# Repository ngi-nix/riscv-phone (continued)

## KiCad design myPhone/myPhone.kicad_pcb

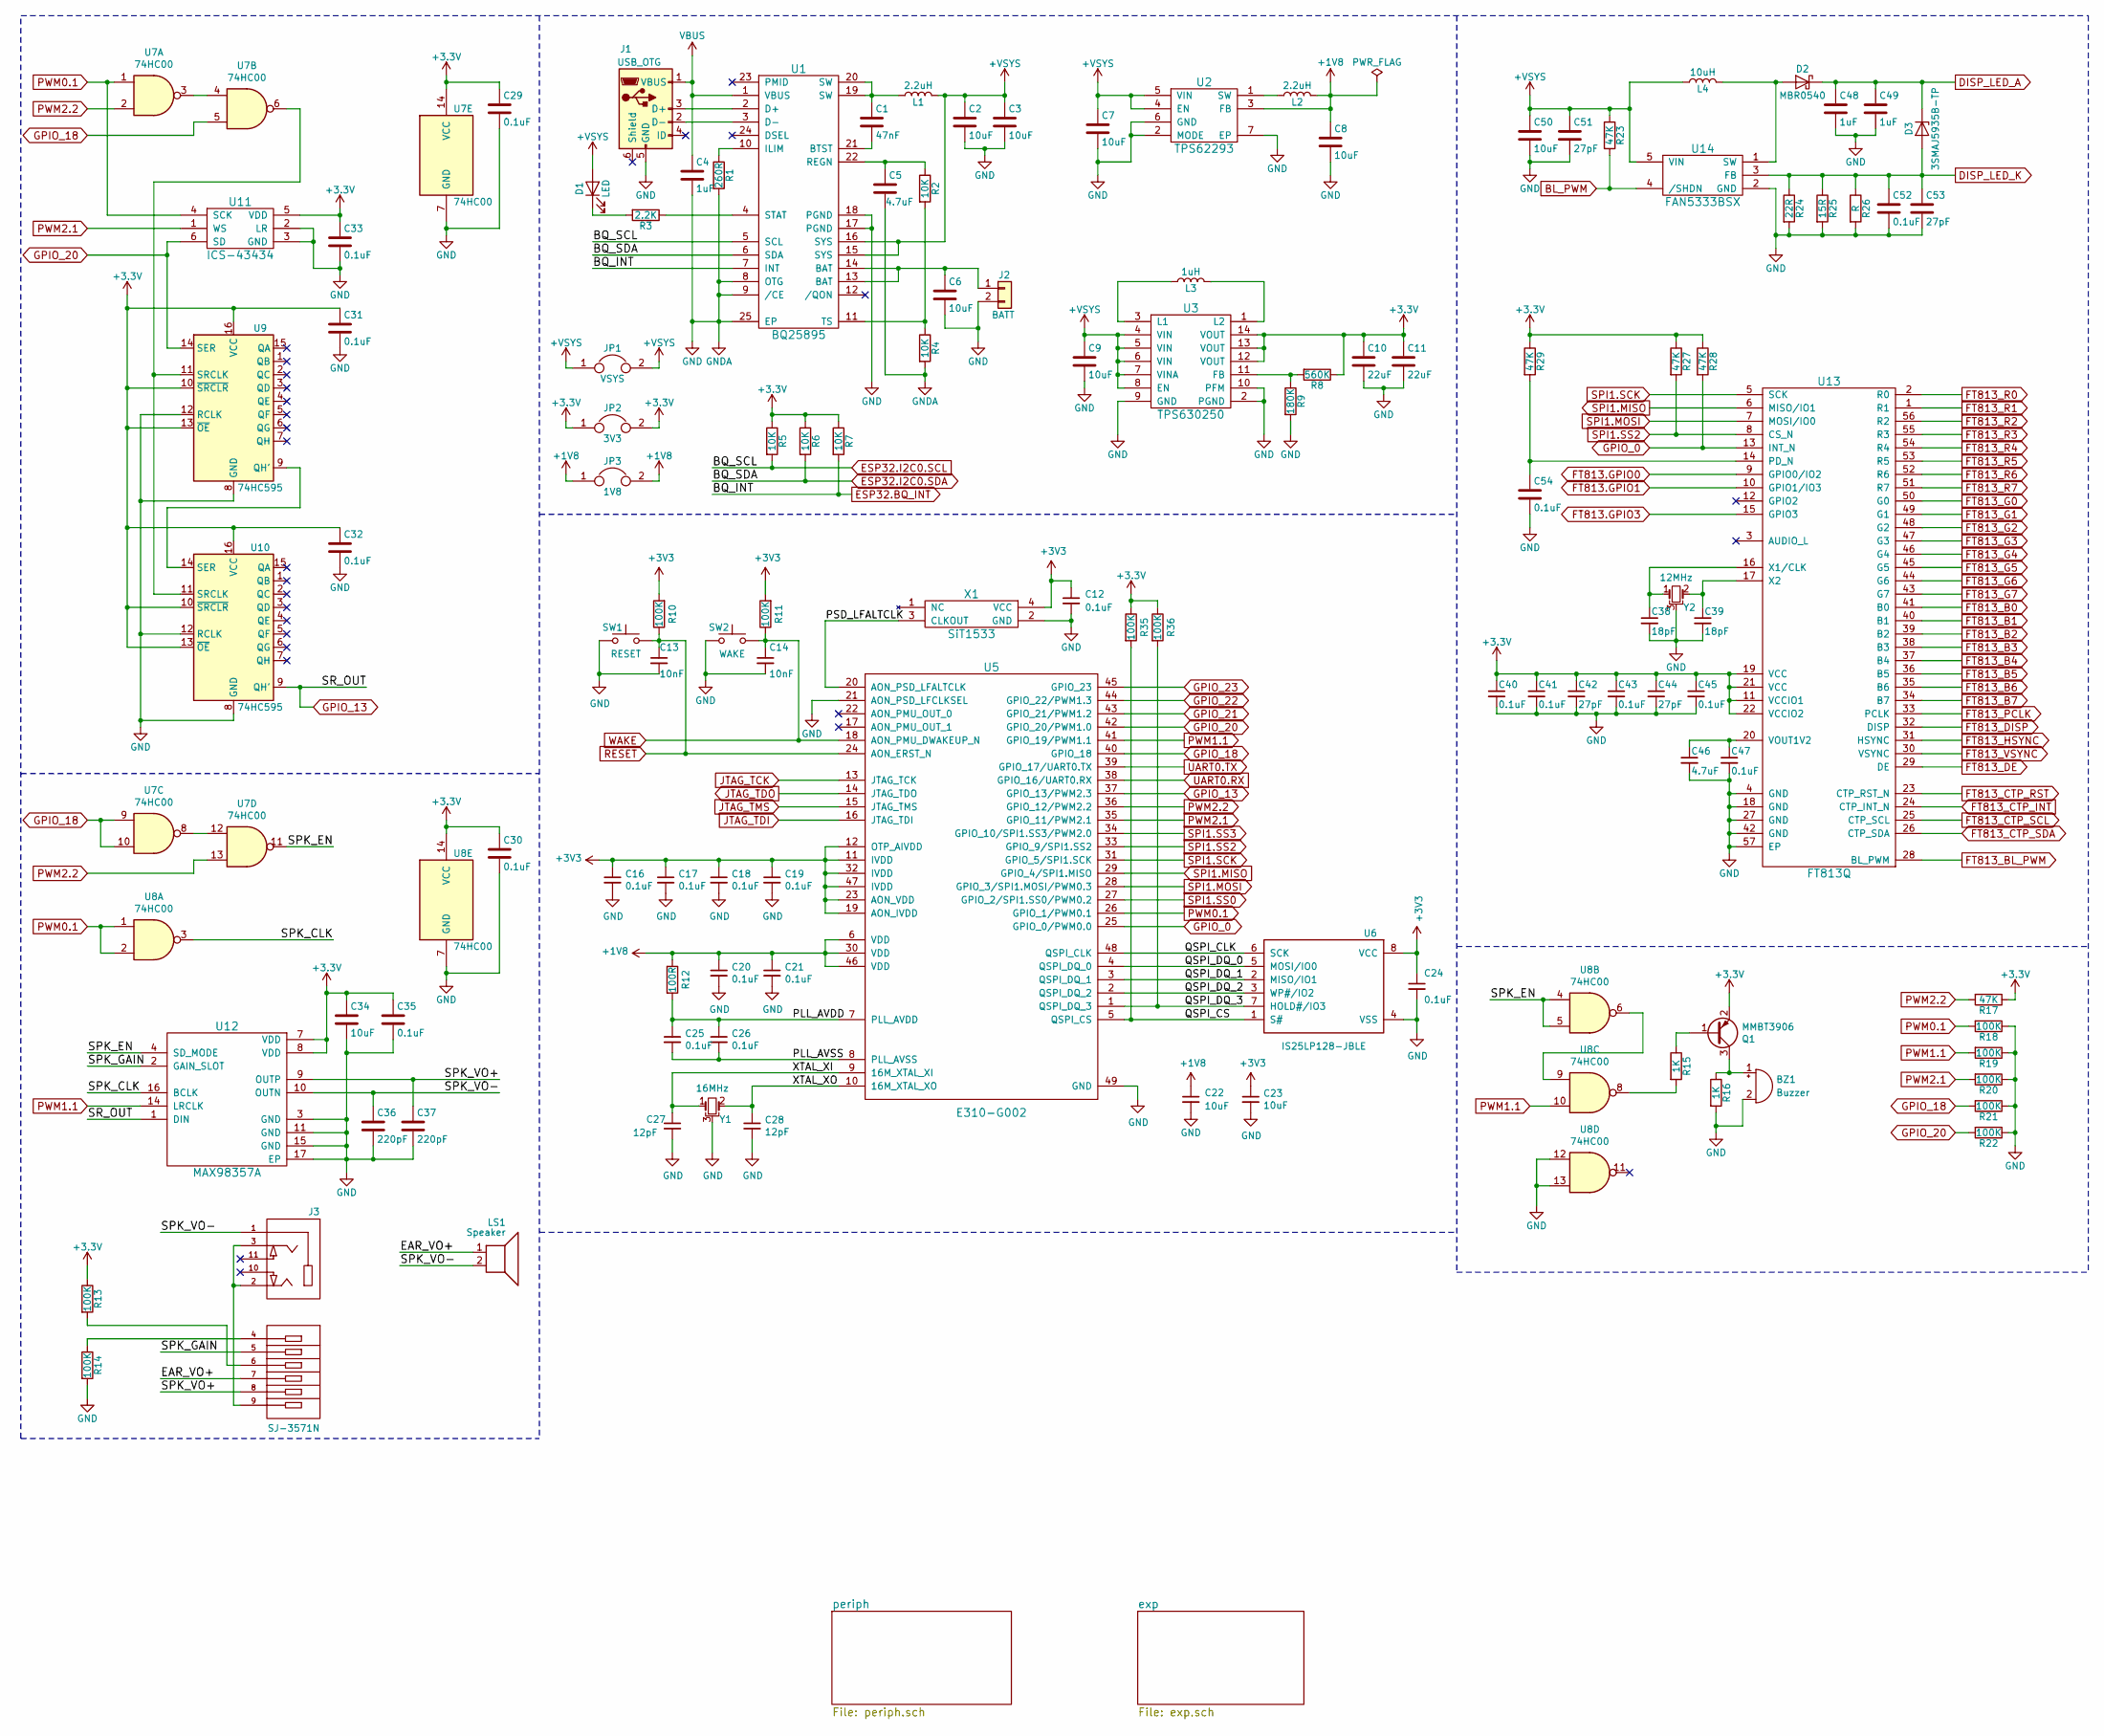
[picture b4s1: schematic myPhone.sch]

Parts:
BZ1: Buzzer; Buzzer_12x9.5RM5.0
C1: 47nF; C_0603_1608Metric
C2, C3, C6, C7, C8, C9, C22, C23, C34, C50: 10uF; C_0603_1608Metric
C4, C48, C49: 1uF; C_0603_1608Metric
C5, C46: 4.7uF; C_0603_1608Metric
C10, C11: 22uF; C_0603_1608Metric
C12, C16, C17, C18, C19, C20, C21, C24, C25, C26, C29, C30, C31, C32, C33, C35, C40, C41, C43, C45, C47, C52, C54: 0.1uF; C_0603_1608Metric
C13, C14: 10nF; C_0603_1608Metric
C27, C28: 12pF; C_0603_1608Metric
C36, C37: 220pF; C_0603_1608Metric
C38, C39: 18pF; C_0603_1608Metric
C42, C44, C51, C53: 27pF; C_0603_1608Metric
D1: LED; LED_0603_1608Metric
D2: MBR0540; D_SOD-123
D3: 3SMAJ5935B-TP; D_SMA
J1: USB_OTG; USB_Micro-B
J2: BATT; PinHeader_1x02_P2.00mm_Vertical
J3: SJ-3571N; CUI_SJ-3571N
JP1: VSYS; PinHeader_1x02_P1.27mm_Vertical
JP2: 3V3; PinHeader_1x02_P1.27mm_Vertical
JP3: 1V8; PinHeader_1x02_P1.27mm_Vertical
L1, L2: 2.2uH; L_Coilcraft_LPS3015
L3: 1uH; L_Coilcraft_XAL40
L4: 10uH; L_Murata_LQH66SN
LS1: Speaker; PinHeader_1x02_P1.27mm_Vertical
Q1: MMBT3906; SOT-23
R1: 260R; R_0603_1608Metric
R2, R4, R5, R6, R7: 10K; R_0603_1608Metric
R3: 2.2K; R_0603_1608Metric
R8: 560K; R_0603_1608Metric
R9: 180K; R_0603_1608Metric
R10, R11, R13, R14, R18, R19, R20, R21, R22, R35, R36: 100K; R_0603_1608Metric
R12: 100R; R_0603_1608Metric
R15, R16: 1K; R_0603_1608Metric
R17, R23, R27, R28, R29: 47K; R_0603_1608Metric
R24: 22R; R_0603_1608Metric
R25: 15R; R_0603_1608Metric
R26: R; R_0603_1608Metric
SW1: RESET; Panasonic_EVPBB
SW2: WAKE; Panasonic_EVPAK
U1: BQ25895; Texas_S-PWQFN-N24_EP2.7x2.7mm_ThermalVias
U2: TPS62293; TPS62290
U3: TPS630250
U5: E310-G002; QFN-48-1EP_6x6mm_P0.4mm_EP4.2x4.2mm_ThermalVias
U6: IS25LP128-JBLE; SOIJ-8_5.3x5.3mm_P1.27mm
U7, U8: 74HC00; 74HC00BQ115
U9, U10: 74HC595; 74HC595BQ115
U11: ICS-43434; TDK_ICS-43434
U12: MAX98357A; TQFN-16-1EP_3x3mm_P0.5mm_EP1.23x1.23mm_ThermalVias
U13: FT813Q; QFN-56-1EP_8x8mm_P0.5mm_EP5.6x5.6mm_ThermalVias
U14: FAN5333BSX; SOT-23-5
X1: SiT1533
Y1: 16MHz; TXC_7M
Y2: 12MHz; TXC_7M

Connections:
+1V8: C8.1, C20.1, C21.1, C22.1, JP3.1, JP3.2, L2.2, R12.1, U2.3 (FB), U5.6 (VDD), U5.30 (VDD), U5.46 (VDD); also elsewhere on the board
+VSYS: C2.1, C3.1, C7.1, C9.1, C50.1, C51.1, D1.2 (A), JP1.1, JP1.2, L1.2, L4.1, R23.1, U1.15 (SYS), U1.16 (SYS), U2.4 (EN), U2.5 (VIN), U3.4 (VIN), U3.5 (VIN), U3.6 (VIN), U3.7 (VINA), U3.8 (EN), U14.5 (VIN); also elsewhere on the board
/EAR_VO+: J3.7, LS1.1
/PLL_AVDD: C25.1, C26.1, R12.2, U5.7 (PLL_AVDD)
/PLL_AVSS: C25.2, C26.2, U5.8 (PLL_AVSS)
/PSD_LFALTCLK: U5.20 (AON_PSD_LFALTCLK), X1.3 (CLKOUT)
/QSPI_CLK: U5.48 (QSPI_CLK), U6.6 (SCK)
/QSPI_CS: R35.2, U5.5 (QSPI_CS), U6.1 (S#)
/QSPI_DQ_0: U5.4 (QSPI_DQ_0), U6.5 (MOSI/IO0)
/QSPI_DQ_1: U5.3 (QSPI_DQ_1), U6.2 (MISO/IO1)
/QSPI_DQ_2: U5.2 (QSPI_DQ_2), U6.3 (WP#/IO2)
/QSPI_DQ_3: R36.2, U5.1 (QSPI_DQ_3), U6.7 (HOLD#/IO3)
/SPK_CLK: U8.3, U12.16 (BCLK)
/SPK_EN: U7.11, U8.4, U8.5, U12.4 (SD_MODE); also elsewhere on the board
/SPK_GAIN: J3.5, U12.2 (GAIN_SLOT)
/SPK_VO+: C37.1, J3.8, U12.9 (OUTP)
/SPK_VO-: C36.1, J3.1, LS1.2, U12.10 (OUTN)
/XTAL_XI: C27.1, U5.9 (16M_XTAL_XI), Y1.1
/XTAL_XO: C28.1, U5.10 (16M_XTAL_XO), Y1.2
BL_PWM: R23.2, U14.4 (/SHDN); also elsewhere on the board
DISP_LED_A: C48.1, C49.1, D2.1 (K), D3.1 (K); also elsewhere on the board
DISP_LED_K: C52.1, C53.1, D3.2 (A), R24.1, R25.1, R26.1, U14.3 (FB); also elsewhere on the board
ESP32.IO39: R7.2, U1.7 (INT); also elsewhere on the board
FT813.GPIO0: U13.9 (GPIO0/IO2); also elsewhere on the board
FT813.GPIO1: U13.10 (GPIO1/IO3); also elsewhere on the board
FT813.GPIO3: U13.15 (GPIO3); also elsewhere on the board
FT813_B0: U13.41 (B0); also elsewhere on the board
FT813_B1: U13.40 (B1); also elsewhere on the board
FT813_B2: U13.39 (B2); also elsewhere on the board
FT813_B3: U13.38 (B3); also elsewhere on the board
FT813_B4: U13.37 (B4); also elsewhere on the board
FT813_B5: U13.36 (B5); also elsewhere on the board
FT813_B6: U13.35 (B6); also elsewhere on the board
FT813_B7: U13.34 (B7); also elsewhere on the board
FT813_BL_PWM: U13.28 (BL_PWM); also elsewhere on the board
FT813_CTP_INT: U13.24 (CTP_INT_N); also elsewhere on the board
FT813_CTP_RST: U13.23 (CTP_RST_N); also elsewhere on the board
FT813_CTP_SCL: U13.25 (CTP_SCL); also elsewhere on the board
FT813_CTP_SDA: U13.26 (CTP_SDA); also elsewhere on the board
FT813_DE: U13.29 (DE); also elsewhere on the board
FT813_DISP: U13.32 (DISP); also elsewhere on the board
FT813_G0: U13.50 (G0); also elsewhere on the board
FT813_G1: U13.49 (G1); also elsewhere on the board
FT813_G2: U13.48 (G2); also elsewhere on the board
FT813_G3: U13.47 (G3); also elsewhere on the board
FT813_G4: U13.46 (G4); also elsewhere on the board
FT813_G5: U13.45 (G5); also elsewhere on the board
FT813_G6: U13.44 (G6); also elsewhere on the board
FT813_G7: U13.43 (G7); also elsewhere on the board
FT813_HSYNC: U13.31 (HSYNC); also elsewhere on the board
FT813_PCLK: U13.33 (PCLK); also elsewhere on the board
FT813_R0: U13.2 (R0); also elsewhere on the board
FT813_R1: U13.1 (R1); also elsewhere on the board
FT813_R2: U13.56 (R2); also elsewhere on the board
FT813_R3: U13.55 (R3); also elsewhere on the board
FT813_R4: U13.54 (R4); also elsewhere on the board
FT813_R5: U13.53 (R5); also elsewhere on the board
FT813_R6: U13.52 (R6); also elsewhere on the board
FT813_R7: U13.51 (R7); also elsewhere on the board
FT813_VSYNC: U13.30 (VSYNC); also elsewhere on the board
GND: BZ1.2 (+), C2.2, C3.2, C4.2, C5.2, C6.2, C7.2, C8.2, C9.2, C10.2, C11.2, C12.2, C13.2, C14.2, C16.2, C17.2, C18.2, C19.2, C20.2, C21.2, C22.2, C23.2, C24.2, C27.2, C28.2, C29.2, C30.2, C31.2, C32.2, C33.2, C34.2, C35.2, C36.2, C37.2, C38.2, C39.2, C40.2, C41.2, C42.2, C43.2, C44.2, C45.2, C46.2, C47.2, C48.2, C49.2, C50.2, C51.2, C52.2, C53.2, C54.2, J1.5 (GND), J2.2, R1.2, R4.2, R9.2, R14.2, R16.2, R18.1, R19.1, R20.1, R21.1, R22.1, R24.2, R25.2, R26.2, SW1.1, SW2.2, U1.8 (OTG), U1.9 (/CE), U1.17 (PGND), U1.18 (PGND), U1.25 (EP), U2.2 (MODE), U2.6 (GND), U2.7 (EP), U3.2 (PGND), U3.9 (GND), U3.10 (PFM), U5.21 (AON_PSD_LFCLKSEL), U5.49 (GND), U6.4 (VSS), U7.7 (GND), U8.7 (GND), U8.12, U8.13, U9.8 (GND), U9.12 (RCLK), U10.8 (GND), U10.12 (RCLK), U11.2 (LR), U11.3 (GND), U12.3 (GND), U12.11 (GND), U12.15 (GND), U12.17 (EP), U13.4 (GND), U13.18 (GND), U13.27 (GND), U13.42 (GND), U13.57 (EP), U14.2 (GND), X1.2 (GND), Y1.3, Y2.3; also elsewhere on the board
GPIO_0: R28.2, U5.25 (GPIO_0/PWM0.0), U13.13 (INT_N)
GPIO_18: R21.2, U5.40 (GPIO_18), U7.5, U7.9, U7.10
GPIO_22: U5.44 (GPIO_22/PWM1.3); also elsewhere on the board
GPIO_23: U5.45 (GPIO_23); also elsewhere on the board
JTAG_TCK: U5.13 (JTAG_TCK); also elsewhere on the board
JTAG_TDI: U5.16 (JTAG_TDI); also elsewhere on the board
JTAG_TDO: U5.14 (JTAG_TDO); also elsewhere on the board
JTAG_TMS: U5.15 (JTAG_TMS); also elsewhere on the board
unnamed: BZ1.1 (-), Q1.3 (C), R16.1
unnamed: C1.1, L1.1, U1.19 (SW), U1.20 (SW)
unnamed: C1.2, U1.21 (BTST)
unnamed: C5.1, R2.1, U1.22 (REGN)
unnamed: C6.1, J2.1, U1.13 (BAT), U1.14 (BAT)
unnamed: C38.1, U13.16 (X1/CLK), Y2.1
unnamed: C39.1, U13.17 (X2), Y2.2
unnamed: C46.1, C47.1, U13.20 (VOUT1V2)
unnamed: C54.1, R29.2, U13.14 (PD_N)
unnamed 176: U1.23 (PMID); also elsewhere on the board
unnamed: D1.1 (K), R3.2
unnamed: D2.2 (A), L4.2, U14.1 (SW)
unnamed: J1.2 (D-), U1.3 (D-)
unnamed: J1.3 (D+), U1.2 (D+)
unnamed: J3.2, J3.3, J3.9
unnamed: J3.4, R14.1
unnamed: J3.6, R13.2
unnamed: L2.1, U2.1 (SW)
unnamed: L3.1, U3.3 (L1)
unnamed: L3.2, U3.1 (L2)
unnamed: Q1.1 (B), R15.1
unnamed: R1.1, U1.10 (ILIM)
unnamed: R2.2, R4.1, U1.11 (TS)
unnamed: R3.1, U1.4 (STAT)
unnamed: R8.2, R9.1, U3.11 (FB)
unnamed: R15.2, U8.8
unnamed: U7.3, U7.4
unnamed: U7.8, U7.12
unnamed: U8.6, U8.9
unnamed: U7.6, U9.11 (SRCLK), U10.11 (SRCLK)
unnamed: U9.9 (QH'), U10.14 (SER)
PWM0.1: R18.2, U5.26 (GPIO_1/PWM0.1), U7.1, U8.1, U8.2, U11.4 (SCK)
RESET: C13.1, R10.1, SW1.2, U5.24 (AON_ERST_N); also elsewhere on the board
SPI1.MISO: U5.29 (GPIO_4/SPI1.MISO), U13.6 (MISO/IO1); also elsewhere on the board
SPI1.MOSI: U5.28 (GPIO_3/SPI1.MOSI/PWM0.3), U13.7 (MOSI/IO0); also elsewhere on the board
SPI1.SCK: U5.31 (GPIO_5/SPI1.SCK), U13.5 (SCK); also elsewhere on the board
SPI1.SS0: U5.27 (GPIO_2/SPI1.SS0/PWM0.2); also elsewhere on the board
SPI1.SS2: R27.2, U5.33 (GPIO_9/SPI1.SS2), U13.8 (CS_N)
SPI1.SS3: U5.34 (GPIO_10/SPI1.SS3/PWM2.0); also elsewhere on the board
TMUX.I2C0.SCL: R5.2, U1.5 (SCL); also elsewhere on the board
TMUX.I2C0.SDA: R6.2, U1.6 (SDA); also elsewhere on the board
UART0.RX: U5.38 (GPIO_16/UART0.RX); also elsewhere on the board
UART0.TX: U5.39 (GPIO_17/UART0.TX); also elsewhere on the board
VBUS: C4.1, J1.1 (VBUS), U1.1 (VBUS)
WAKE: C14.1, R11.1, SW2.1, U1.12 (/QON), U5.18 (AON_PMU_DWAKEUP_N); also elsewhere on the board

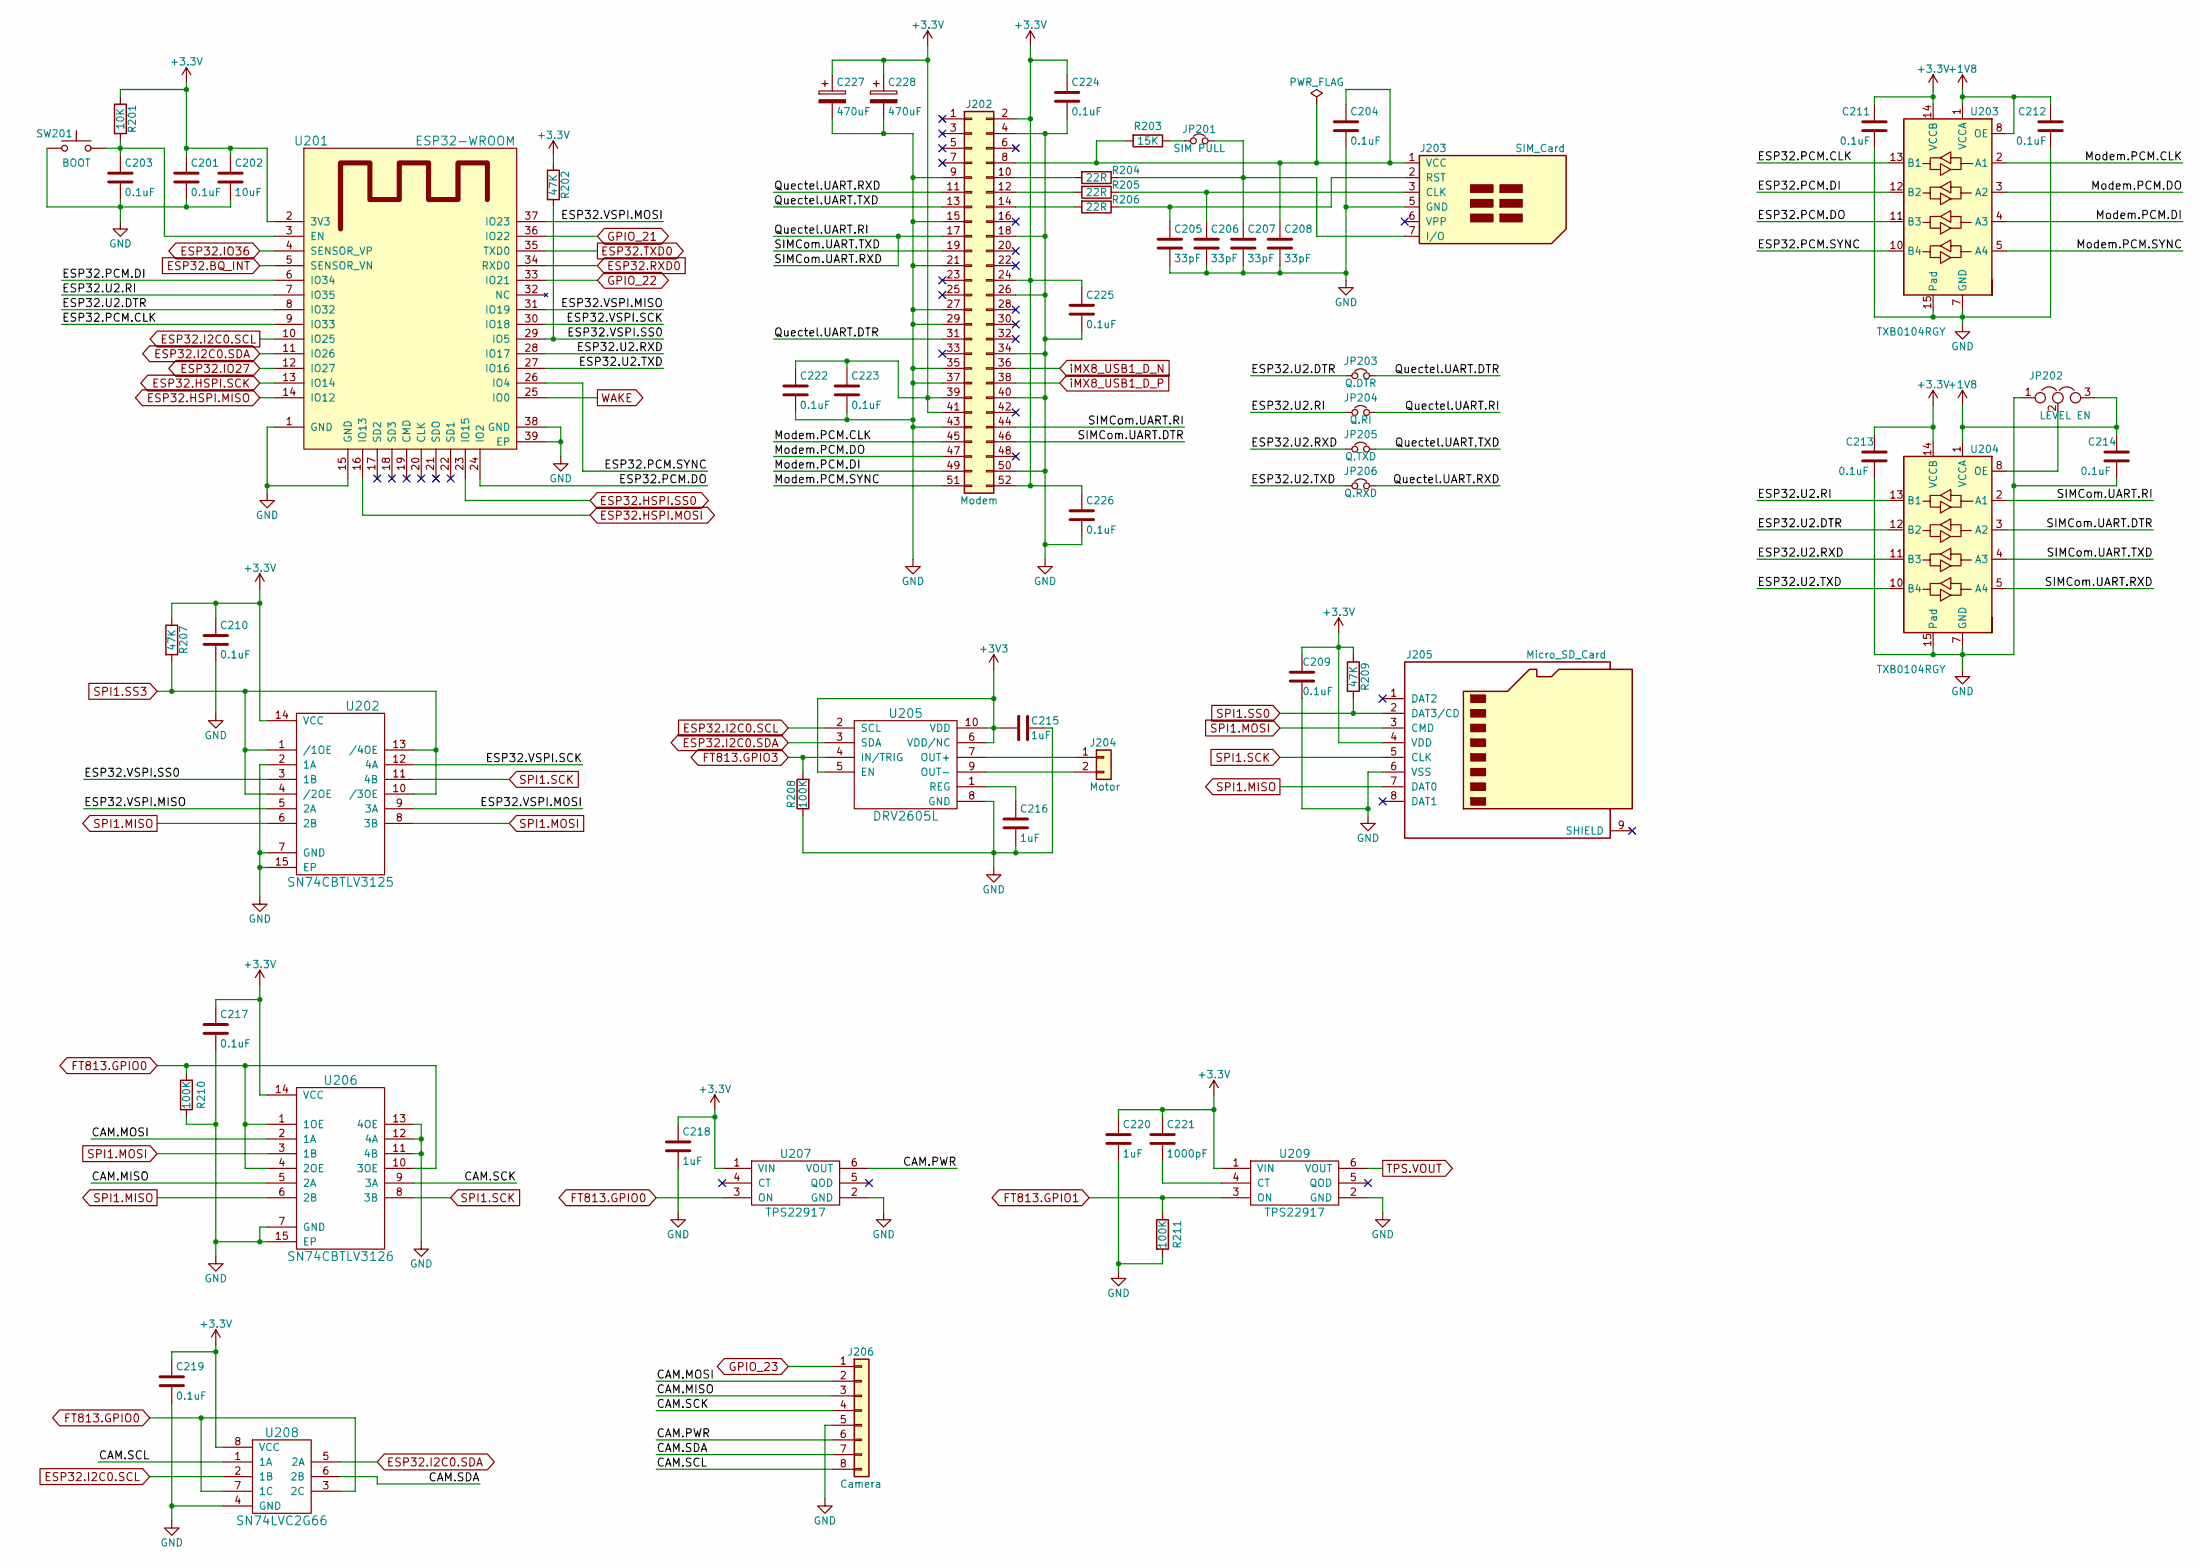
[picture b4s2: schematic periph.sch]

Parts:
C201, C203, C204, C209, C210, C211, C212, C213, C214, C217, C219, C222, C223, C224, C225, C226: 0.1uF; C_0603_1608Metric
C202: 10uF; C_0603_1608Metric
C205, C206, C207, C208: 33pF; C_0603_1608Metric
C215, C216, C218, C220: 1uF; C_0603_1608Metric
C221: 1000pF; C_0603_1608Metric
C227, C228: 470uF; CP_EIA-3528-21_Kemet-B
J202: Modem; mpcie-socket
J203: SIM_Card; Wurth_NanoSIM-693043020611
J204: Motor; PinHeader_1x02_P1.27mm_Vertical
J205: Micro_SD_Card; MicroSd
J206: Camera; PinHeader_1x08_P2.54mm_Vertical
JP201: SIM PULL; PinHeader_1x02_P1.27mm_Vertical
JP202: LEVEL EN; PinHeader_1x03_P1.27mm_Vertical
JP203: Q.DTR; PinHeader_1x02_P1.27mm_Vertical
JP204: Q.RI; PinHeader_1x02_P1.27mm_Vertical
JP205: Q.TXD; PinHeader_1x02_P1.27mm_Vertical
JP206: Q.RXD; PinHeader_1x02_P1.27mm_Vertical
R201: 10K; R_0603_1608Metric
R202, R207, R209: 47K; R_0603_1608Metric
R203: 15K; R_0603_1608Metric
R204, R205, R206: 22R; R_0603_1608Metric
R208, R210, R211: 100K; R_0603_1608Metric
SW201: BOOT; Panasonic_EVPBB
U201: ESP32-WROOM
U202: SN74CBTLV3125; Texas_S-PVQFN-N14_ThermalVias
U203, U204: TXB0104RGY; Texas_S-PVQFN-N14_ThermalVias
U205: DRV2605L; VSSOP-10_3x3mm_P0.5mm
U206: SN74CBTLV3126; Texas_S-PVQFN-N14_ThermalVias
U207, U209: TPS22917; Texas_R-PDSO-G6
U208: SN74LVC2G66; VSSOP-8_2.4x2.1mm_P0.5mm

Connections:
+1V8: C212.1, C214.1, JP202.3, U203.1 (VCCA), U203.8 (OE), U204.1 (VCCA); also elsewhere on the board
/periph/CAM.MISO: J206.3, U206.5 (2A)
/periph/CAM.MOSI: J206.2, U206.2 (1A)
/periph/CAM.PWR: J206.6, U207.6 (VOUT)
/periph/CAM.SCK: J206.4, U206.9 (3A)
/periph/CAM.SCL: J206.8, U208.1 (1A)
/periph/CAM.SDA: J206.7, U208.6 (2B)
/periph/ESP32.PCM.CLK: U201.9 (IO33), U203.13 (B1)
/periph/ESP32.PCM.DI: U201.6 (IO34), U203.12 (B2)
/periph/ESP32.PCM.DO: U201.24 (IO2), U203.11 (B3)
/periph/ESP32.PCM.SYNC: U201.26 (IO4), U203.10 (B4)
/periph/ESP32.U2.DTR: JP203.1, U201.8 (IO32), U204.12 (B2)
/periph/ESP32.U2.RI: JP204.1, U201.7 (IO35), U204.13 (B1)
/periph/ESP32.U2.RXD: JP205.1, U201.28 (IO17), U204.11 (B3)
/periph/ESP32.U2.TXD: JP206.1, U201.27 (IO16), U204.10 (B4)
/periph/ESP32.VSPI.MISO: U201.31 (IO19), U202.5 (2A)
/periph/ESP32.VSPI.MOSI: U201.37 (IO23), U202.9 (3A)
/periph/ESP32.VSPI.SCK: U201.30 (IO18), U202.12 (4A)
/periph/ESP32.VSPI.SS0: R202.2, U201.29 (IO5), U202.3 (1B)
/periph/Modem.PCM.CLK: J202.45, U203.2 (A1)
/periph/Modem.PCM.DI: J202.49, U203.4 (A3)
/periph/Modem.PCM.DO: J202.47, U203.3 (A2)
/periph/Modem.PCM.SYNC: J202.51, U203.5 (A4)
/periph/Quectel.UART.DTR: J202.31, JP203.2
/periph/Quectel.UART.RI: J202.17, JP204.2, U204.5 (A4)
/periph/Quectel.UART.RXD: J202.11, JP206.2
/periph/Quectel.UART.TXD: J202.13, JP205.2
/periph/SIMCom.UART.DTR: J202.46, U204.3 (A2)
/periph/SIMCom.UART.RI: J202.44, U204.2 (A1)
/periph/SIMCom.UART.TXD: J202.19, U204.4 (A3)
ESP32.HSPI.MISO: U201.14 (IO12); also elsewhere on the board
ESP32.HSPI.MOSI: U201.16 (IO13); also elsewhere on the board
ESP32.HSPI.SCK: U201.13 (IO14); also elsewhere on the board
ESP32.HSPI.SS0: U201.23 (IO15); also elsewhere on the board
ESP32.IO27: U201.12 (IO27); also elsewhere on the board
ESP32.IO36: U201.4 (SENSOR_VP); also elsewhere on the board
ESP32.IO39: U201.5 (SENSOR_VN); also elsewhere on the board
ESP32.RXD0: U201.34 (RXD0); also elsewhere on the board
ESP32.TXD0: U201.35 (TXD0); also elsewhere on the board
FT813.GPIO0: R210.2, U206.1 (1OE), U206.4 (2OE), U206.10 (3OE), U207.3 (ON), U208.3 (2C), U208.7 (1C); also elsewhere on the board
FT813.GPIO1: R211.1, U209.3 (ON); also elsewhere on the board
FT813.GPIO3: R208.2, U205.4 (IN/TRIG); also elsewhere on the board
GND: C201.2, C202.2, C203.2, C204.2, C205.2, C206.2, C207.2, C208.2, C209.2, C210.2, C211.2, C212.2, C213.2, C214.2, C215.1, C216.2, C217.2, C218.2, C219.2, C220.2, C222.2, C223.2, C224.2, C225.2, C226.2, C227.2, C228.2, J202.4, J202.9, J202.15, J202.18, J202.21, J202.26, J202.27, J202.29, J202.34, J202.35, J202.37, J202.40, J202.43, J202.50, J203.5 (GND), J205.6 (VSS), J206.5, JP202.1, R208.1, R210.1, R211.2, SW201.2, U201.1 (GND), U201.15 (GND), U201.38 (GND), U201.39 (EP), U202.2 (1A), U202.7 (GND), U202.15 (EP), U203.7 (GND), U203.15 (Pad), U204.7 (GND), U204.15 (Pad), U205.8 (GND), U206.7 (GND), U206.11 (4B), U206.12 (4A), U206.13 (4OE), U206.15 (EP), U207.2 (GND), U208.4 (GND), U209.2 (GND); also elsewhere on the board
GPIO_22: U201.33 (IO21); also elsewhere on the board
GPIO_23: J206.1; also elsewhere on the board
unnamed: C203.1, R201.2, SW201.1, U201.3 (EN)
unnamed: C204.1, C208.1, J202.8, J203.1 (VCC), R203.2
unnamed: C205.1, J203.2 (RST), R206.1
unnamed: C206.1, J203.3 (CLK), R205.1
unnamed: C207.1, J203.7 (I/O), JP201.2, R204.1
unnamed: C216.1, U205.1 (REG)
unnamed: C221.2, U209.4 (CT)
unnamed: J202.10, R204.2
unnamed: J202.12, R205.2
unnamed: J202.14, R206.2
unnamed: J204.1, U205.7 (OUT+)
unnamed: J204.2, U205.9 (OUT-)
unnamed: JP201.1, R203.1
unnamed: JP202.2, U204.8 (OE)
SPI1.MISO: J205.7 (DAT0), U202.6 (2B), U206.6 (2B); also elsewhere on the board
SPI1.MOSI: J205.3 (CMD), U202.8 (3B), U206.3 (1B); also elsewhere on the board
SPI1.SCK: J205.5 (CLK), U202.11 (4B), U206.8 (3B); also elsewhere on the board
SPI1.SS0: J205.2 (DAT3/CD), R209.2; also elsewhere on the board
SPI1.SS3: R207.2, U202.1 (/1OE), U202.4 (/2OE), U202.10 (/3OE), U202.13 (/4OE); also elsewhere on the board
TMUX.I2C0.SCL: U201.10 (IO25), U205.2 (SCL), U208.2 (1B); also elsewhere on the board
TMUX.I2C0.SDA: U201.11 (IO26), U205.3 (SDA), U208.5 (2A); also elsewhere on the board
TPS.VOUT: U209.6 (VOUT); also elsewhere on the board
WAKE: U201.25 (IO0); also elsewhere on the board
iMX8_USB1_D_N: J202.36; also elsewhere on the board
iMX8_USB1_D_P: J202.38; also elsewhere on the board
